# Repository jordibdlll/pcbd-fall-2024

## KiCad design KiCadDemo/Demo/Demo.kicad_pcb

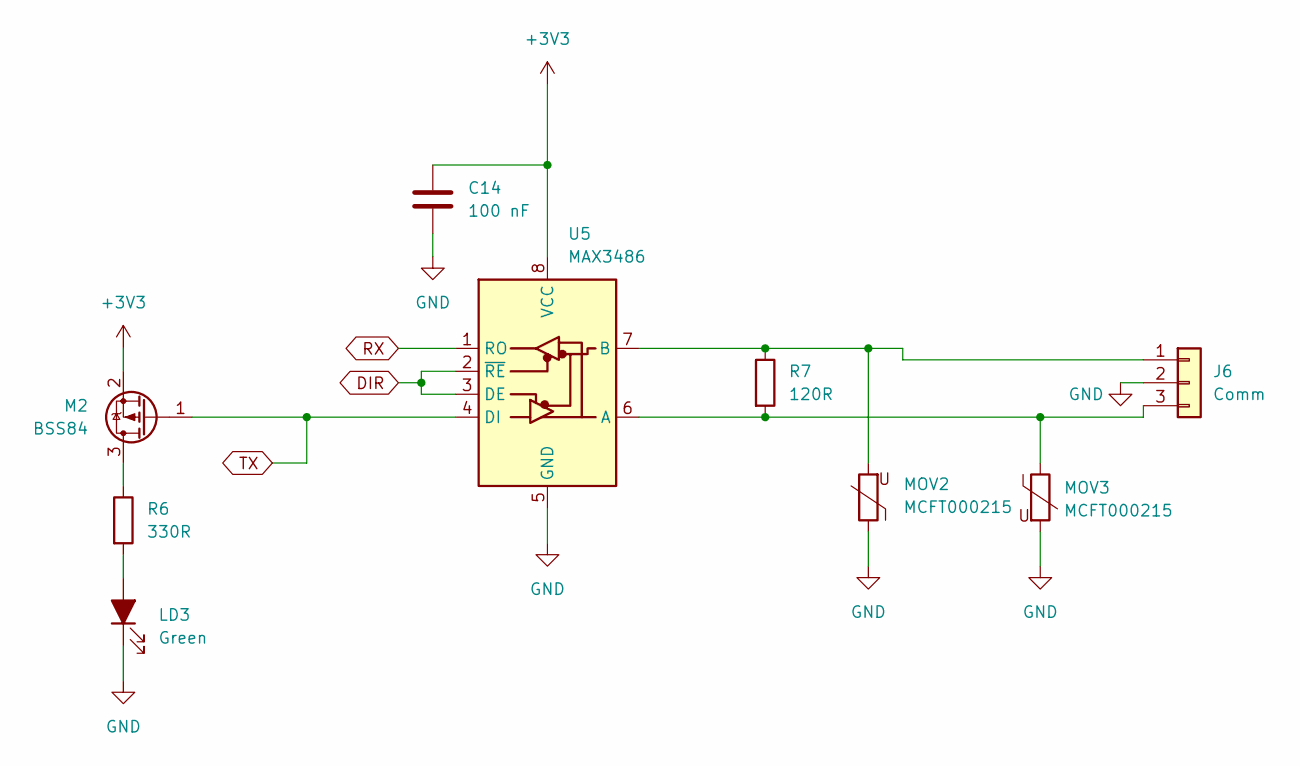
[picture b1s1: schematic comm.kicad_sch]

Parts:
C14: 100 nF; C_0805_2012Metric
J6: Comm; IO3
LD3: Green; LED_D5.0mm
M2: BSS84; SOT-23
MOV2, MOV3: MCFT000215; RV_Disc_D7mm_W3.4mm_P5mm
R6: 330R; R_1206_3216Metric
R7: 120R; R_1206_3216Metric
U5: MAX3486; SOIC-8_3.9x4.9mm_P1.27mm

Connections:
+3V3: C14.1, M2.2 (S), U5.8 (VCC); also elsewhere on the board
DIR: U5.2 (~RE), U5.3 (DE); also elsewhere on the board
GND: C14.2, J6.2, LD3.1 (K), MOV2.1, MOV3.2, U5.5 (GND); also elsewhere on the board
unnamed: J6.1, MOV2.2, R7.1, U5.7 (B)
unnamed: J6.3, MOV3.1, R7.2, U5.6 (A)
unnamed: LD3.2 (A), R6.2
unnamed: M2.3 (D), R6.1
RX: U5.1 (RO); also elsewhere on the board
TX: M2.1 (G), U5.4 (DI); also elsewhere on the board

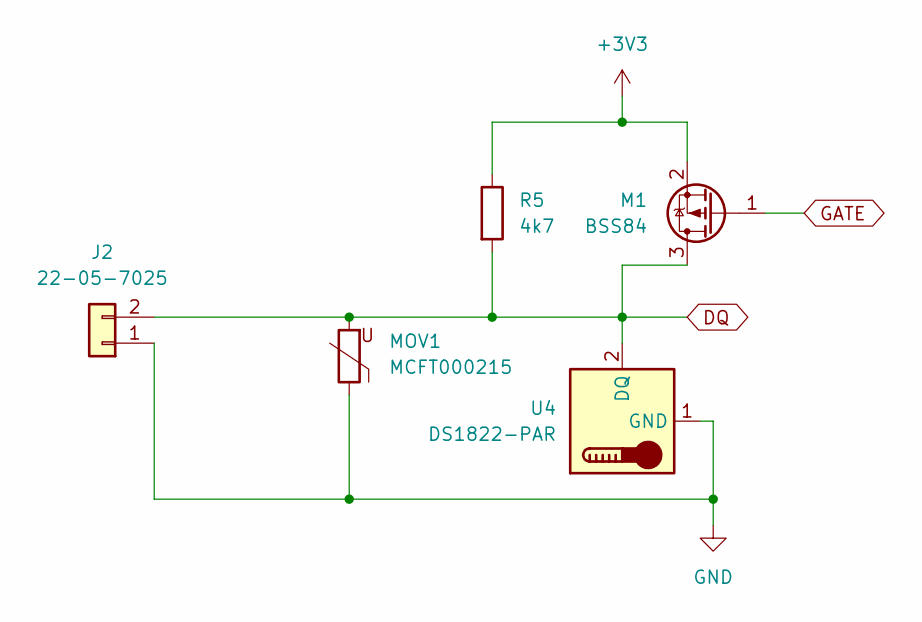
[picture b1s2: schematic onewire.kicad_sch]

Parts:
J2: 22-05-7025; IO2
M1: BSS84; SOT-23
MOV1: MCFT000215; RV_Disc_D7mm_W3.4mm_P5mm
R5: 4k7; R_0805_2012Metric
U4: DS1822-PAR; TO-92_Inline

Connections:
+3V3: M1.2 (S), R5.1; also elsewhere on the board
DQ: J2.2, M1.3 (D), MOV1.2, R5.2, U4.2 (DQ); also elsewhere on the board
GATE: M1.1 (G); also elsewhere on the board
GND: J2.1, MOV1.1, U4.1 (GND); also elsewhere on the board

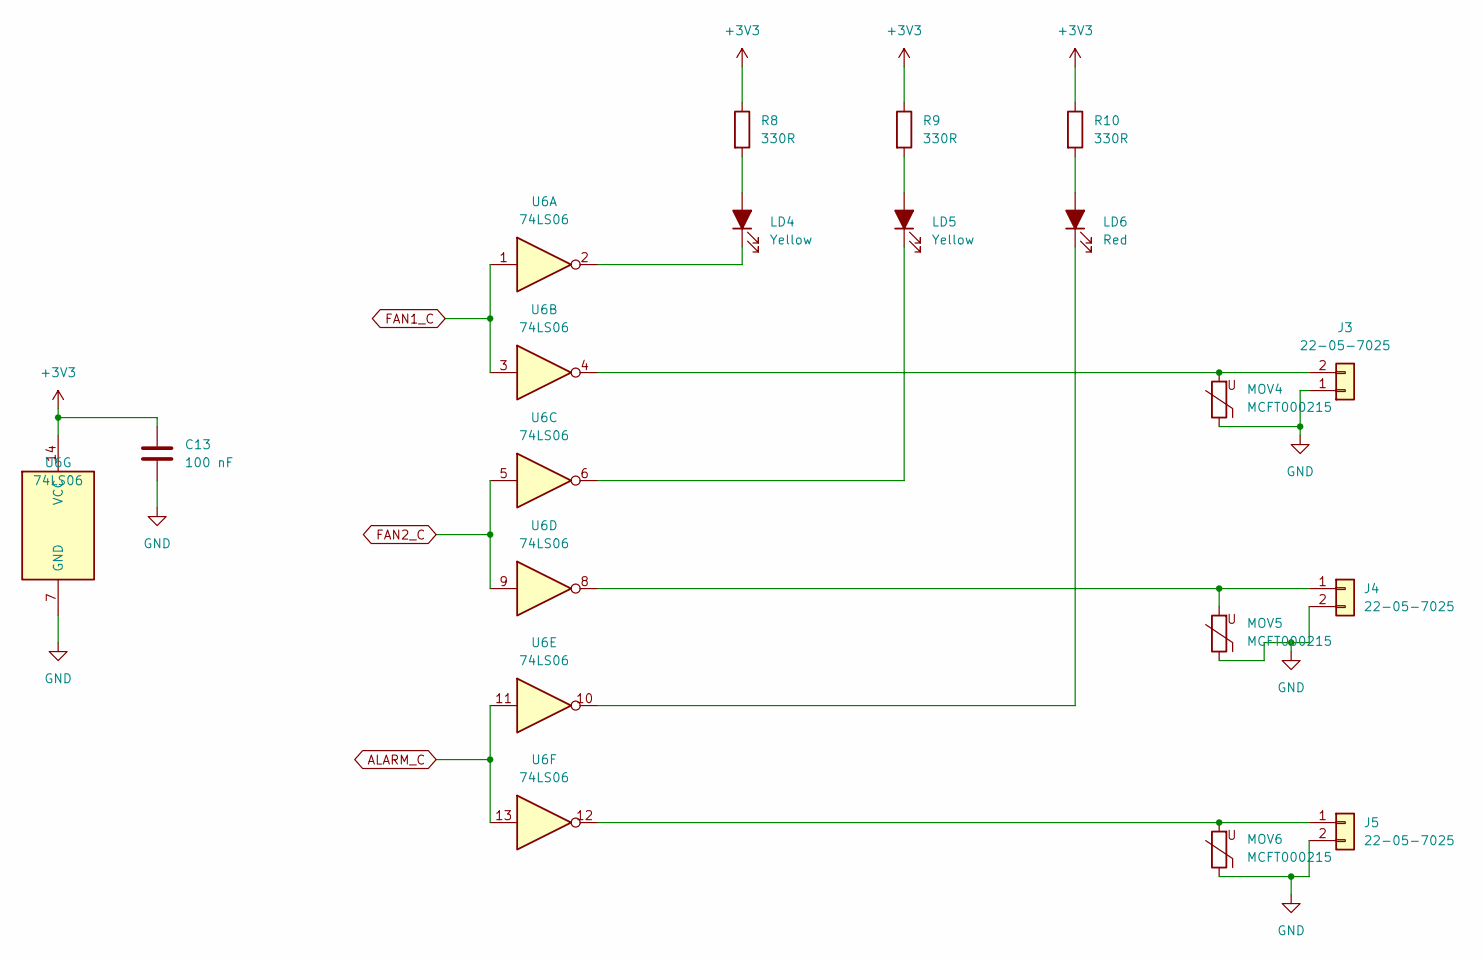
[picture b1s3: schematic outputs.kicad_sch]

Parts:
C13: 100 nF; C_0805_2012Metric
J3, J4, J5: 22-05-7025; IO2
LD4, LD5: Yellow; LED_D5.0mm
LD6: Red; LED_D5.0mm
MOV4, MOV5, MOV6: MCFT000215; RV_Disc_D7mm_W3.4mm_P5mm
R8, R9, R10: 330R; R_1206_3216Metric
U6: 74LS06; SOIC-14_3.9x8.7mm_P1.27mm

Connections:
+3V3: C13.1, R8.1, R9.1, R10.1, U6.14 (VCC); also elsewhere on the board
ALARM_C: U6.11, U6.13; also elsewhere on the board
FAN1_C: U6.1, U6.3; also elsewhere on the board
FAN2_C: U6.5, U6.9; also elsewhere on the board
GND: C13.2, J3.1, J4.2, J5.2, MOV4.1, MOV5.1, MOV6.1, U6.7 (GND); also elsewhere on the board
unnamed: J3.2, MOV4.2, U6.4
unnamed: J4.1, MOV5.2, U6.8
unnamed: J5.1, MOV6.2, U6.12
unnamed: LD4.2 (A), R8.2
unnamed: LD4.1 (K), U6.2
unnamed: LD5.2 (A), R9.2
unnamed: LD5.1 (K), U6.6
unnamed: LD6.2 (A), R10.2
unnamed: LD6.1 (K), U6.10

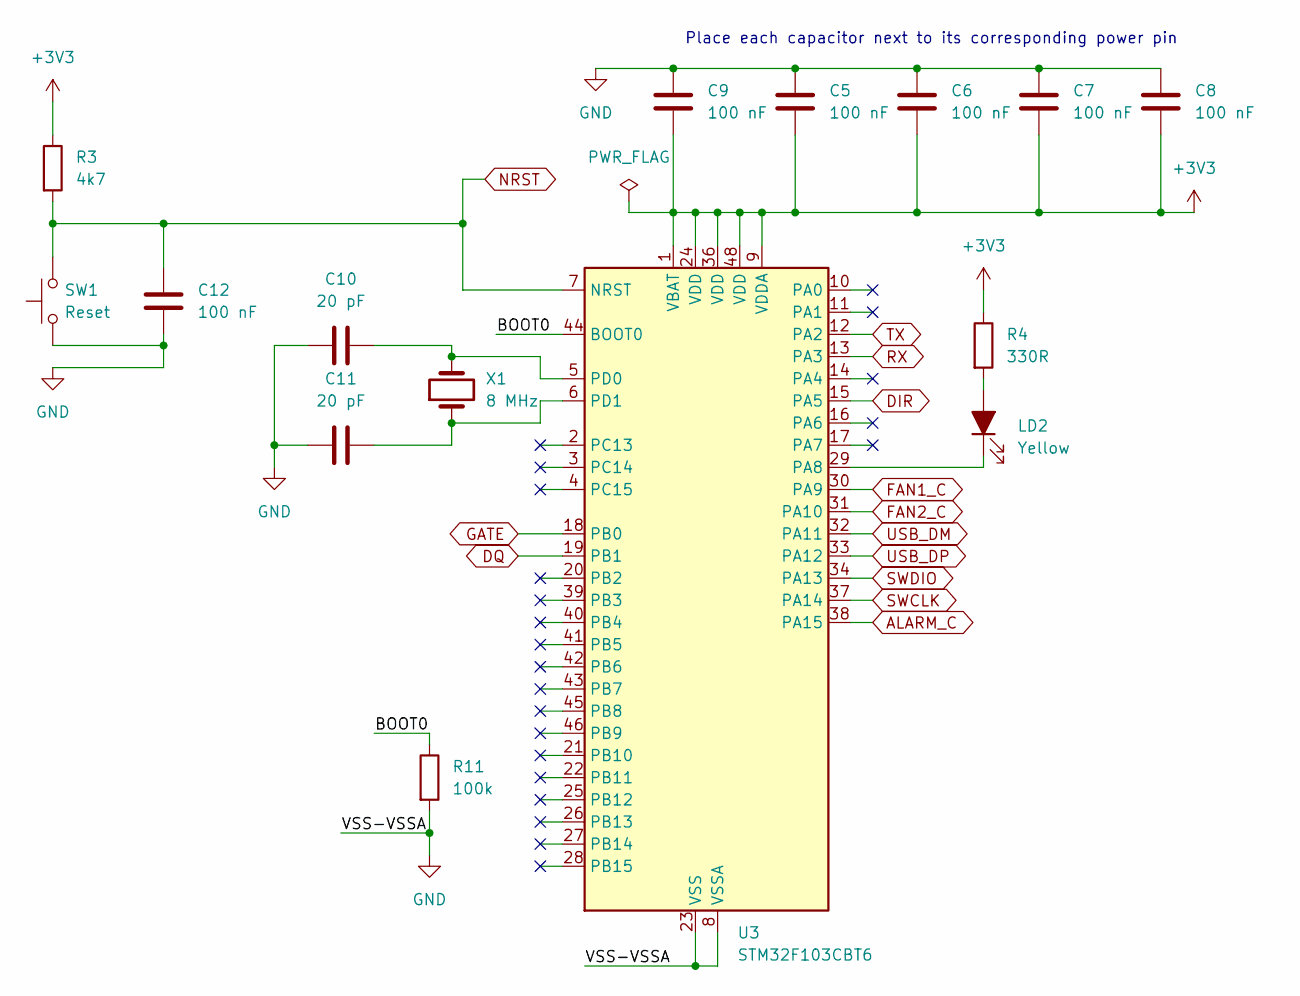
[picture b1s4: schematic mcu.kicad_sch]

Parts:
C5, C6, C7, C8, C9, C12: 100 nF; C_0805_2012Metric
C10, C11: 20 pF; C_0805_2012Metric
LD2: Yellow; LED_D5.0mm
R3: 4k7; R_0805_2012Metric
R4: 330R; R_1206_3216Metric
R11: 100k; R_0805_2012Metric
SW1: Reset
U3: STM32F103CBT6; LQFP-48_7x7mm_P0.5mm
X1: 8 MHz; Crystal_HC18-U_Vertical

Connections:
+3V3: C5.2, C6.2, C7.2, C8.2, C9.2, R3.1, R4.1, U3.1 (VBAT), U3.9 (VDDA), U3.24 (VDD), U3.36 (VDD), U3.48 (VDD); also elsewhere on the board
/mcu/BOOT0: R11.1, U3.44 (BOOT0)
ALARM_C: U3.38 (PA15); also elsewhere on the board
DIR: U3.15 (PA5); also elsewhere on the board
DQ: U3.19 (PB1); also elsewhere on the board
FAN1_C: U3.30 (PA9); also elsewhere on the board
FAN2_C: U3.31 (PA10); also elsewhere on the board
GATE: U3.18 (PB0); also elsewhere on the board
GND: C5.1, C6.1, C7.1, C8.1, C9.1, C10.1, C11.1, C12.2, R11.2, SW1.1, U3.8 (VSSA), U3.23 (VSS), U3.35 (VSS), U3.47 (VSS); also elsewhere on the board
NRST: C12.1, R3.2, SW1.2, U3.7 (NRST); also elsewhere on the board
unnamed: LD2.2 (A), R4.2
unnamed: LD2.1 (K), U3.29 (PA8)
unnamed: C10.2, U3.5 (PD0), X1.2
unnamed: C11.2, U3.6 (PD1), X1.1
RX: U3.13 (PA3); also elsewhere on the board
SWCLK: U3.37 (PA14); also elsewhere on the board
SWDIO: U3.34 (PA13); also elsewhere on the board
TX: U3.12 (PA2); also elsewhere on the board
USB_DM: U3.32 (PA11); also elsewhere on the board
USB_DP: U3.33 (PA12); also elsewhere on the board

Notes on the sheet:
Place each capacitor next to its corresponding power pin

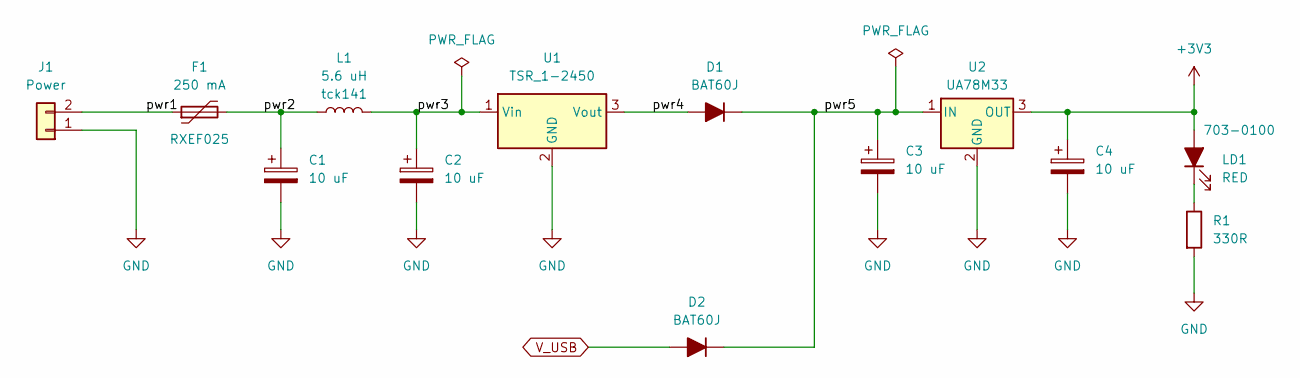
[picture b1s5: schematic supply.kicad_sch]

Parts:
C1, C2, C3, C4: 10 uF; CP_Elec_6.3x5.8
D1, D2: BAT60J; D_SOD-323
F1: 250 mA; R_Axial_DIN0204_L3.6mm_D1.6mm_P5.08mm_Horizontal
J1: Power
L1: 5.6 uH; tck141
LD1: RED; LED_D5.0mm
R1: 330R; R_1206_3216Metric
U1: TSR_1-2450; Converter_DCDC_TRACO_TSR-1_THT
U2: UA78M33; SOT-223-3_TabPin2

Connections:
+3V3: C4.1, LD1.2 (A), U2.3 (OUT); also elsewhere on the board
/supply/pwr1: F1.1, J1.2
/supply/pwr2: C1.1, F1.2, L1.1
/supply/pwr3: C2.1, L1.2, U1.1 (Vin)
/supply/pwr4: D1.2 (A), U1.3 (Vout)
/supply/pwr5: C3.1, D1.1 (K), D2.1 (K), U2.1 (IN)
GND: C1.2, C2.2, C3.2, C4.2, J1.1, R1.2, U1.2 (GND), U2.2 (GND); also elsewhere on the board
unnamed: LD1.1 (K), R1.1
V_USB: D2.2 (A); also elsewhere on the board

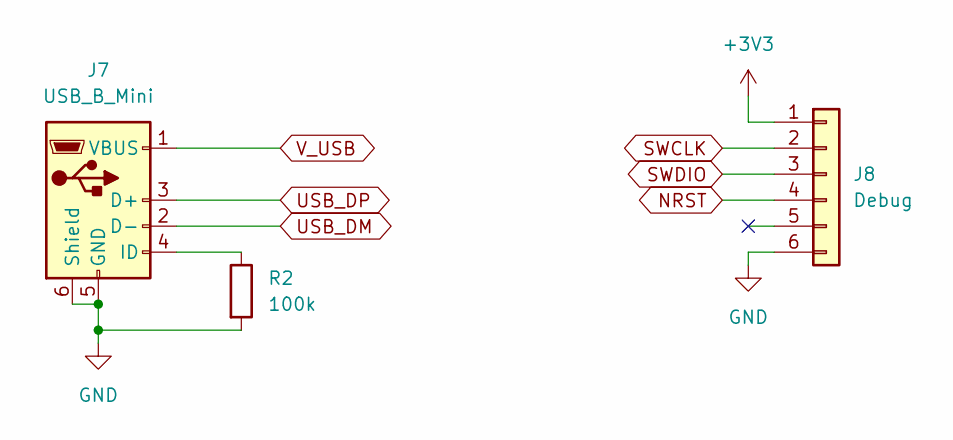
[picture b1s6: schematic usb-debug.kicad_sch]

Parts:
J7: USB_B_Mini; USB_Mini-B_Wuerth_65100516121_Horizontal
J8: Debug
R2: 100k; R_0805_2012Metric

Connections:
+3V3: J8.1; also elsewhere on the board
GND: J7.5 (GND), J7.6 (Shield), J8.6, R2.2; also elsewhere on the board
NRST: J8.4; also elsewhere on the board
unnamed: J7.4 (ID), R2.1
SWCLK: J8.2; also elsewhere on the board
SWDIO: J8.3; also elsewhere on the board
USB_DM: J7.2 (D-); also elsewhere on the board
USB_DP: J7.3 (D+); also elsewhere on the board
V_USB: J7.1 (VBUS); also elsewhere on the board

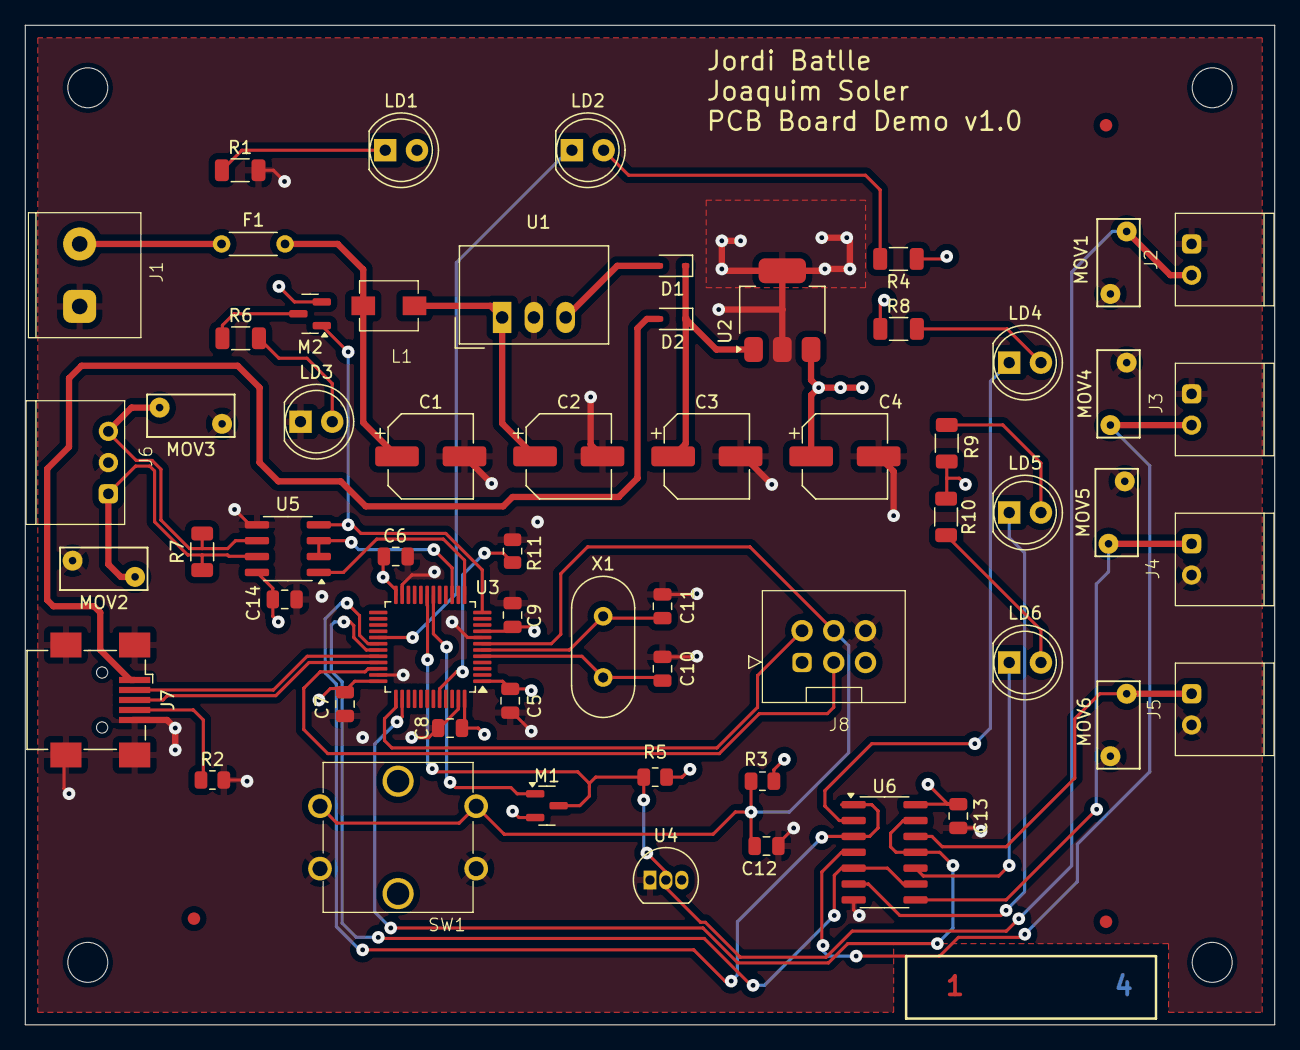
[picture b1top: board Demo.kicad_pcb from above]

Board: 4 copper layers, 100.0 x 80.0 mm, 66 parts (0 on the bottom side), 41 nets.

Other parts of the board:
FD1, FD2, FD3: Fiducial_1mm_Mask2mm
H1, H2, H3, H4: MountingHole_3.2mm_M3

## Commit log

2024-10-06 First commit, included Check #1
2024-10-13 Add files via upload
    Check2 schematics
2024-10-22 Footprints check 3
    Added "Power" footprint, and "IO2" not completed.
2024-10-27 Complete io2, add io3 and debug connector footprints
2024-10-28 Remove elements from top view
2024-10-28 Add files via upload
    Inductor footprint added
2024-10-28 Add button footprint
2024-10-28 Check #4
2024-10-29 Add files via upload
    Placement of the fixed components and mecanical holes
2024-11-03 review button footprint
2024-11-05 Final placement version + fixed debug footprint
    Final placement version + fixed debug footprint
2024-11-12 check5_placementV2
    Replacement of components. Start of the routing
2024-11-12 Moodify component names and text label
2024-11-13 Add files via upload
    Plots generated.
2024-11-16 Start of the routing
    Power lines routed. MCU coupling capacitors routed and also oscillator.
2024-11-17 Follow routing
2024-11-19 check6-routingv2
    Final routing. Added planes at each layer. Left cleaning up and gerbers.
2024-11-26 Add files via upload
    Changes proposed by Vicente made.
2024-12-03 2 layer PCB conversion v1
    2 layer PCB conversion v1
2024-12-12 Optional 2 milled PCB
2024-12-15 Optional 3 HandSolder PCB version
    Optional 3 HandSolder PCB version
